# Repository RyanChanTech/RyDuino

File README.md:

# RyDuino
After using many different microcontrollers through the years, I’ve developed two microcontroller boards based on my own personal preferences and experiences that I've called the RyDuino (a portmanteau of Ryan and Arduino). Specifically, many of the major features are designed to replace things that I commonly have to use breadboards for. Currently, they are both based on the ATmega328P in a DIP package because I like the option of replacing chips if they get damaged. However, I plan on making another version based on the ESP32 chip.

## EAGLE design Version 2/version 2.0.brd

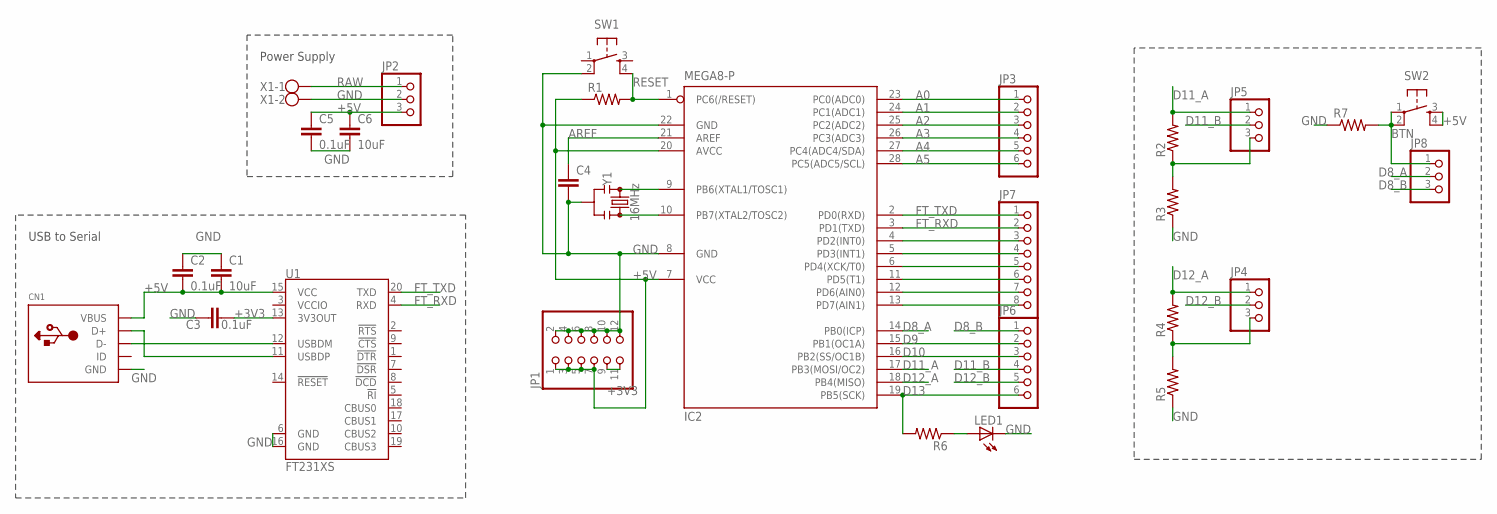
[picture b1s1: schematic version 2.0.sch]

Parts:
C1, C6: 10uF; C0603
C2, C3, C5: 0.1uF; C0603
C4: C-EUC0603; C0603
CN1: USBMINIB; USB-MINIB
IC2: MEGA8-P; DIL28-3
JP1: PINHD-2X6; 2X06
JP2, JP4, JP5, JP8: PINHD-1X3; 1X03
JP3, JP6: PINHD-1X6; 1X06
JP7: PINHD-1X8; 1X08
LED1: LEDCHIP-LED0805; CHIP-LED0805
R1, R2, R3, R4, R5, R6, R7: R-US_R0603; R0603
SW1, SW2: SWITCH_SPST_4_PINRECT; TACTILE_SWITCH_SMD_4.6X2.8MM
U1: FT231XS; SSOP20_L
X1: W237-102
Y1: 16MHz; RESONATOR-SMD-3.2X1.3

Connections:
+3V3: C3.2, JP1.9, JP1.11, U1.13 (3V3OUT)
+5V: C1.2, C2.2, C5.1, C6.1, CN1.VBUS, IC2.7 (VCC), IC2.20 (AVCC), JP1.1, JP1.3, JP1.5, JP1.7, JP2.3, R1.1, SW2.3, SW2.4, U1.15 (VCC)
A0: IC2.23 (PC0(ADC0)), JP3.1
A1: IC2.24 (PC1(ADC1)), JP3.2
A2: IC2.25 (PC2(ADC2)), JP3.3
A3: IC2.26 (PC3(ADC3)), JP3.4
A4: IC2.27 (PC4(ADC4/SDA)), JP3.5
A5: IC2.28 (PC5(ADC5/SCL)), JP3.6
AREF: C4.1, IC2.21 (AREF)
BTN: JP8.1, R7.2, SW2.1, SW2.2
D8_A: IC2.14 (PB0(ICP)), JP8.2
D8_B: JP6.1, JP8.3
D9: IC2.15 (PB1(OC1A)), JP6.2
D10: IC2.16 (PB2(SS/OC1B)), JP6.3
D11_A: IC2.17 (PB3(MOSI/OC2)), JP5.1, R2.2
D11_B: JP5.2, JP6.4
D12_A: IC2.18 (PB4(MISO)), JP4.1, R4.2
D12_B: JP4.2, JP6.5
D13: IC2.19 (PB5(SCK)), JP6.6, R6.2
FT_RXD: IC2.3 (PD1(TXD)), JP7.2, U1.4 (RXD)
FT_TXD: IC2.2 (PD0(RXD)), JP7.1, U1.20 (TXD)
GND: C1.1, C2.1, C3.1, C4.2, C5.2, C6.2, CN1.GND, IC2.8 (GND), IC2.22 (GND), JP1.2, JP1.4, JP1.6, JP1.8, JP1.10, JP1.12, JP2.2, LED1.C, R3.1, R5.1, R7.1, SW1.2, U1.6 (GND), U1.16 (GND), X1.2, Y1.2
unnamed: CN1.D-, U1.12 (USBDM)
unnamed: CN1.D+, U1.11 (USBDP)
unnamed: LED1.A, R6.1
unnamed: IC2.9 (PB6(XTAL1/TOSC1)), Y1.1
unnamed: IC2.10 (PB7(XTAL2/TOSC2)), Y1.3
unnamed: JP5.3, R2.1, R3.2
unnamed: JP4.3, R4.1, R5.2
unnamed: IC2.4 (PD2(INT0)), JP7.3
unnamed: IC2.5 (PD3(INT1)), JP7.4
unnamed: IC2.6 (PD4(XCK/T0)), JP7.5
unnamed: IC2.11 (PD5(T1)), JP7.6
unnamed: IC2.12 (PD6(AIN0)), JP7.7
unnamed: IC2.13 (PD7(AIN1)), JP7.8
RAW: JP2.1, X1.1
RESET: IC2.1 (PC6(/RESET)), R1.2, SW1.4

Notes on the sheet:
USB to Serial
Power Supply

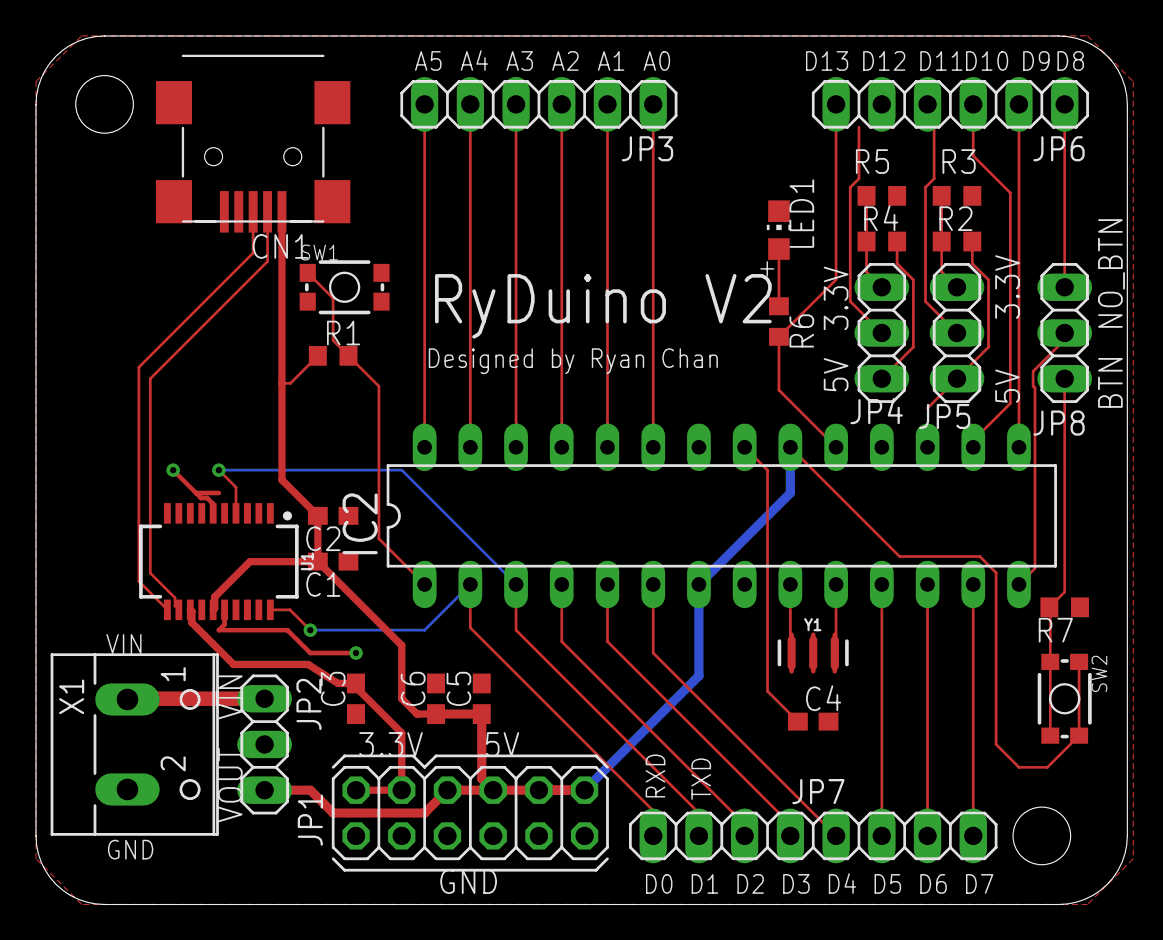
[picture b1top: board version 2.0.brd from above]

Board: 2 copper layers, 60.6 x 48.2 mm, 29 parts (0 on the bottom side), 37 nets.

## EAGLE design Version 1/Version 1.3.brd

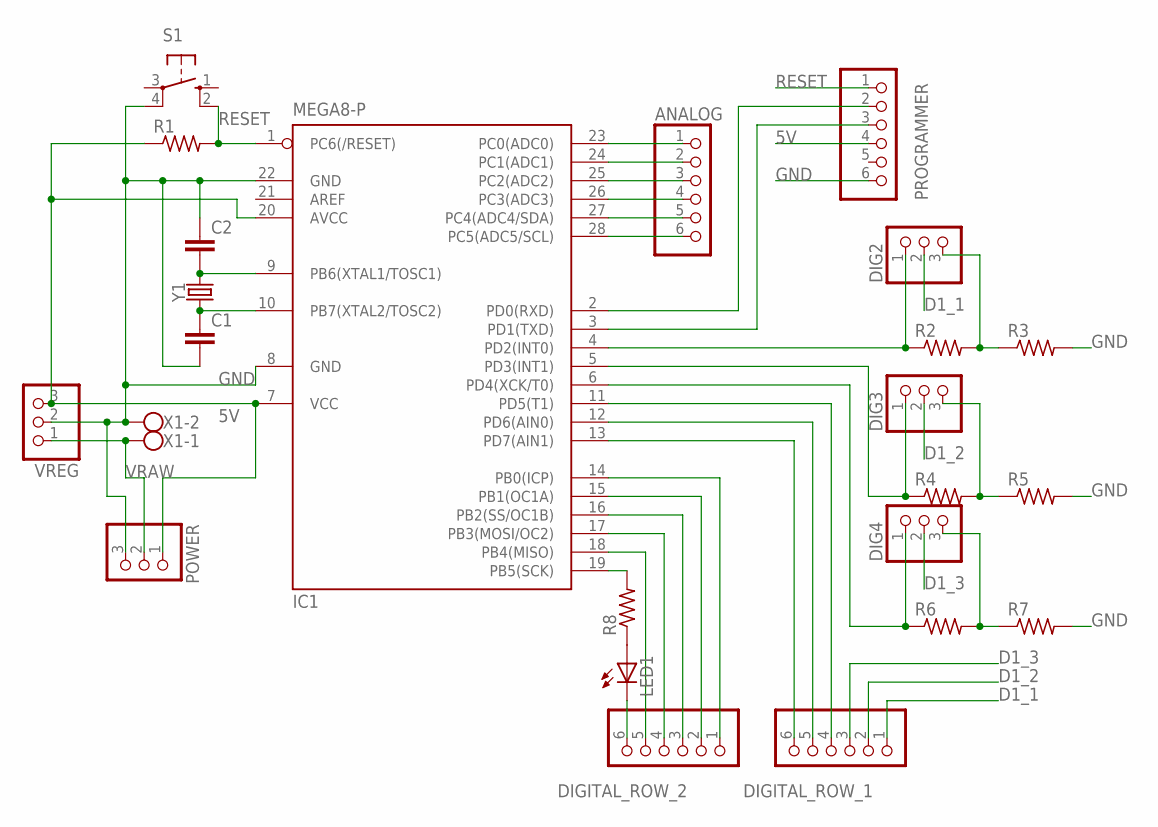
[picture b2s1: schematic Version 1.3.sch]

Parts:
ANALOG: PINHD-1X6B; 1X06-BIG
C1, C2: C2,5-3; C2.5-3
DIG2, DIG3, DIG4: PINHD-1X3; 1X03
DIGITAL_ROW_1, DIGITAL_ROW_2: PINHD-1X6B; 1X06-BIG
IC1: MEGA8-P; DIL28-3
LED1: LED3MM
POWER: PINHD-1X3; 1X03
PROGRAMMER: PINHD-1X6B; 1X06-BIG
R1, R2, R3, R4, R5, R6, R7, R8: R-US_0204/7; 0204/7
S1: 10-XX; B3F-10XX
VREG: PINHD-1X3CB; 1X03-CLEANBIG
X1: W237-102
Y1: CRYSTALPTH-HC49US; HC49US

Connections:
5V: IC1.7 (VCC), IC1.20 (AVCC), POWER.1, PROGRAMMER.4, R1.1, VREG.3
D1_1: DIG2.2, DIGITAL_ROW_1.1
D1_2: DIG3.2, DIGITAL_ROW_1.2
D1_3: DIG4.2, DIGITAL_ROW_1.3
GND: C1.2, C2.1, IC1.8 (GND), IC1.22 (GND), POWER.3, PROGRAMMER.6, R3.2, R5.2, R7.2, S1.4 (P1), VREG.2, X1.2
unnamed: C2.2, IC1.9 (PB6(XTAL1/TOSC1)), Y1.2
unnamed: C1.1, IC1.10 (PB7(XTAL2/TOSC2)), Y1.1
unnamed: DIG2.3, R2.2, R3.1
unnamed: LED1.A, R8.1
unnamed: ANALOG.1, IC1.23 (PC0(ADC0))
unnamed: ANALOG.2, IC1.24 (PC1(ADC1))
unnamed: IC1.2 (PD0(RXD)), PROGRAMMER.2
unnamed: IC1.3 (PD1(TXD)), PROGRAMMER.3
unnamed: ANALOG.3, IC1.25 (PC2(ADC2))
unnamed: ANALOG.4, IC1.26 (PC3(ADC3))
unnamed: ANALOG.5, IC1.27 (PC4(ADC4/SDA))
unnamed: ANALOG.6, IC1.28 (PC5(ADC5/SCL))
unnamed: DIG3.1, IC1.5 (PD3(INT1)), R4.1
unnamed: DIGITAL_ROW_1.6, IC1.13 (PD7(AIN1))
unnamed: DIGITAL_ROW_1.5, IC1.12 (PD6(AIN0))
unnamed: DIGITAL_ROW_1.4, IC1.11 (PD5(T1))
unnamed: DIG3.3, R4.2, R5.1
unnamed: DIGITAL_ROW_2.1, IC1.14 (PB0(ICP))
unnamed: DIGITAL_ROW_2.2, IC1.15 (PB1(OC1A))
unnamed: DIGITAL_ROW_2.3, IC1.16 (PB2(SS/OC1B))
unnamed: DIGITAL_ROW_2.4, IC1.17 (PB3(MOSI/OC2))
unnamed: DIGITAL_ROW_2.5, IC1.18 (PB4(MISO))
unnamed: IC1.19 (PB5(SCK)), R8.2
unnamed: DIG2.1, IC1.4 (PD2(INT0)), R2.1
unnamed: DIG4.1, IC1.6 (PD4(XCK/T0)), R6.1
unnamed: DIG4.3, R6.2, R7.1
unnamed: DIGITAL_ROW_2.6, LED1.K (C)
RESET: IC1.1 (PC6(/RESET)), PROGRAMMER.1, R1.2, S1.2 (S1)
VRAW: POWER.2, VREG.1, X1.1

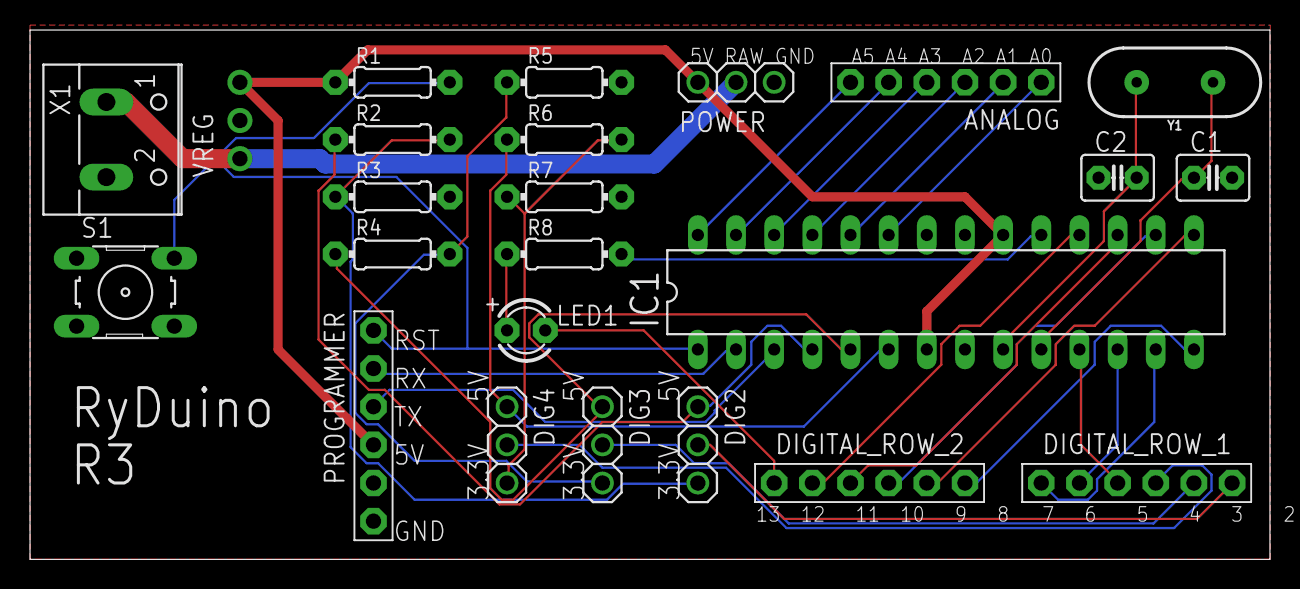
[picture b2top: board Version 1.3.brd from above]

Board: 2 copper layers, 82.5 x 35.2 mm, 24 parts (0 on the bottom side), 34 nets.

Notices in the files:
parts and their libraries:
SparkFun-Clocks: Licensing: Creative Commons ShareAlike 4.0 International - https://creativecommons.org/licenses/by-sa/4.0
